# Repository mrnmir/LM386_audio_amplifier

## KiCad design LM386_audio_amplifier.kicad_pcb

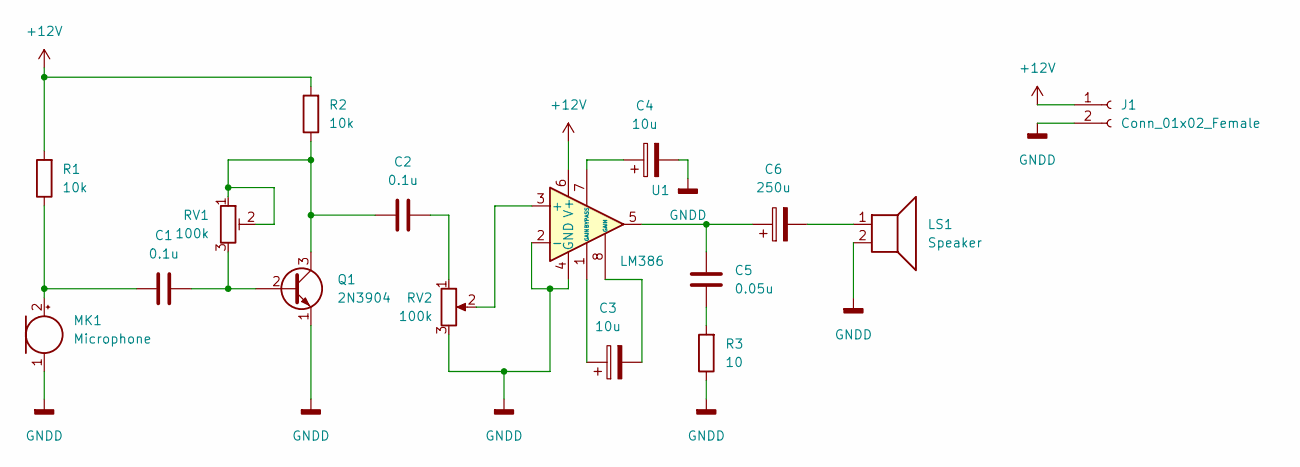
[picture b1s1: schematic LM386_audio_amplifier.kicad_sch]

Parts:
C1, C2: 0.1u; C_Disc_D5.1mm_W3.2mm_P5.00mm
C3, C4: 10u; CP_Radial_D8.0mm_P3.80mm
C5: 0.05u; C_Disc_D5.1mm_W3.2mm_P5.00mm
C6: 250u; CP_Radial_D8.0mm_P3.80mm
J1: Conn_01x02_Female; PinHeader_1x02_P2.54mm_Vertical
LS1: Speaker; PinHeader_1x02_P2.54mm_Vertical
MK1: Microphone; PinHeader_1x02_P2.54mm_Vertical
Q1: 2N3904; TO-92_Inline_Wide
R1, R2: 10k; R_Axial_DIN0309_L9.0mm_D3.2mm_P15.24mm_Horizontal
R3: 10; R_Axial_DIN0309_L9.0mm_D3.2mm_P15.24mm_Horizontal
RV1: 100k; Potentiometer_Bourns_3296P_Horizontal
RV2: 100k; Potentiometer_Alps_RK163_Single_Horizontal
U1: LM386; DIP-8_W7.62mm_LongPads

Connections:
+12V: J1.1, R1.2, R2.2, U1.6 (V+)
GNDD: C4.2, J1.2, LS1.2, MK1.1 (-), Q1.1 (E), R3.1, RV2.3, U1.2 (-), U1.4 (GND)
unnamed: C1.1, MK1.2 (+), R1.1
unnamed: C1.2, Q1.2 (B), RV1.3
unnamed: C2.1, Q1.3 (C), R2.1, RV1.1, RV1.2
unnamed: C2.2, RV2.1
unnamed: C3.1, U1.1 (GAIN)
unnamed: C3.2, U1.8 (GAIN)
unnamed: C4.1, U1.7 (BYPASS)
unnamed: C5.1, R3.2
unnamed: C5.2, C6.1, U1.5
unnamed: C6.2, LS1.1
unnamed: RV2.2, U1.3 (+)

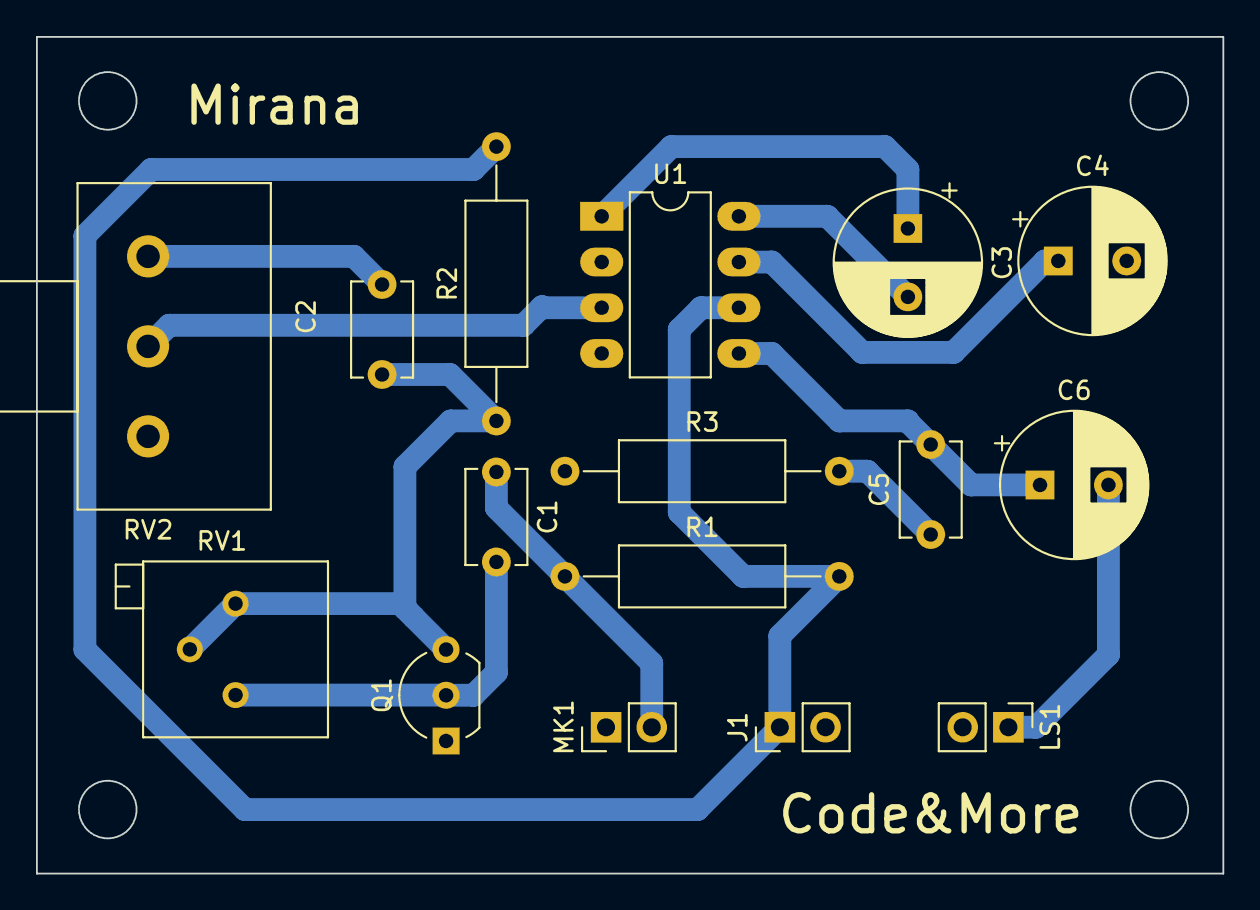
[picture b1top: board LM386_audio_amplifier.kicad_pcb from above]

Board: 2 copper layers, 65.9 x 46.5 mm, 16 parts (0 on the bottom side), 13 nets.

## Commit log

2024-02-03 Done
2024-02-03 changed
2024-02-03 some improvements
